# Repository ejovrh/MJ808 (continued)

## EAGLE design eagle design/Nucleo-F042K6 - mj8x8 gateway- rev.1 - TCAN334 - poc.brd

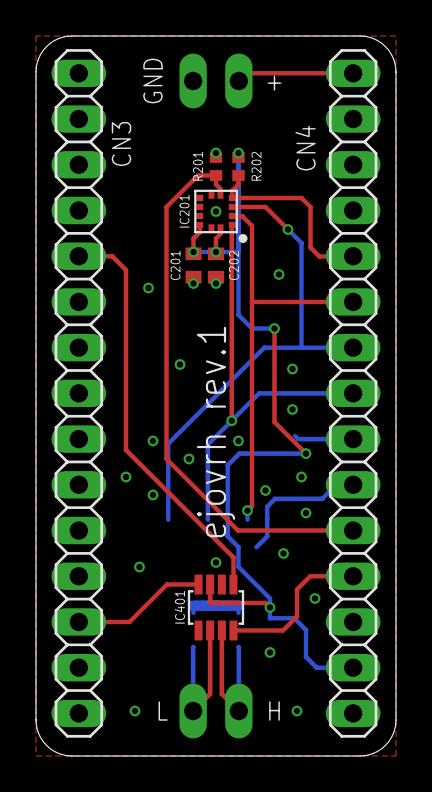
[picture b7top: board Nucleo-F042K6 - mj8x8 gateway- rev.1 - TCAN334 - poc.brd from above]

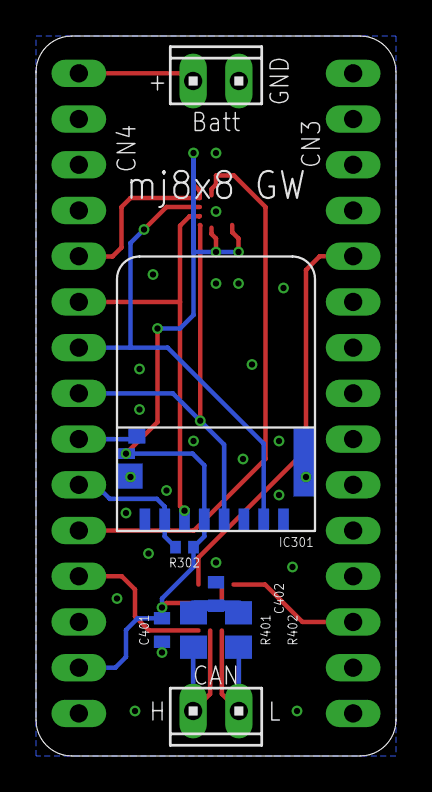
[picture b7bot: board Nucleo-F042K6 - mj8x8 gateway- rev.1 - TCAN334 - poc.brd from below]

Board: 2 copper layers, 20.0 x 40.0 mm, 16 parts (8 on the bottom side), 17 nets.

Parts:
C201, C202: 0.1u; C0402
C401: 0.1uF / 10V; C0402
C402: 47nF / 10V; C0402
IC201: ADXL367; LGA
IC301: 47309-2651; MICRO_SD_CONNECTOR
IC401: TCAN334; SOT23-8
J1, J2: Batt; 10X02MTA
JP1: CN3; 1X15
JP2: CN4; 1X15
R201, R202, R302: 10k; R0402
R401, R402: 60; R0805

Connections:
3V3: C201.1, C202.1, C401.1, IC201.10, IC201.12, IC301.G3, IC301.PIN4, IC401.P$3, JP2.14, R202.2, R302.2
!STBY!: IC401.P$8, JP2.12
ADXL367_CS: IC201.4, JP2.5, R202.1
ADXL367_INT1: IC201.5, JP2.11, R201.2
CANH: IC401.P$7, J2.1, R401.2
CANL: IC401.P$6, J2.2, R402.1
CAN_INFRA:SPLIT: C402.1, R401.1, R402.2
CLK: IC201.1, IC301.PIN5, JP2.8
GND: C201.2, C202.2, C401.2, C402.2, IC201.7, IC201.11, IC301.G1, IC301.G2, IC301.PIN6, IC401.P$2, J1.1, JP1.4, JP2.2, R201.1
MISO: IC201.3, IC301.PIN7, JP2.7
MOSI: IC201.2, IC301.PIN3, JP2.6
RST: JP1.3, JP2.3
RXCAN: IC401.P$4, JP1.13
SD_CS: IC301.PIN2, JP2.10, R302.1
SD_DET: IC301.G4, JP2.9
TXCAN: IC401.P$1, JP1.5
VIN: J1.2, JP2.1
